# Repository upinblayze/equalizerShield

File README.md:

# Graphic Equalizer Shield

> This project is dependent on [Sparkfun](www.sparkfun.com)'s EAGLE libraries and also OSHPark's DRU file.

## Get EAGLE
The EAGLE download can be found [here](https://www.autodesk.com/products EAGLE/free-download). The free version is sufficient in this case
> EAGLE used to be made by CADSOFT USA, but is now under the AutoDesk umbrella.

## Download and apply design rules
We are going to be using [OSHPark's design rules](https://oshpark.com/LaenPCBOrder.dru) since this is the service we are using to make the PCBs. You should expect a file called LaenPCBOrder.dru

## Clone the repository
For the puposes of simplicity, it is recommended that you clone this repository in your $HOME (root) directory. Input the following command in terminal.

`git clone git@github.com:upinblayze/equalizerShield.git`

## Download Sparkfun's EAGLE libraries
They are made for older versions of EAGLE, but they work nonetheless. You may either clone the [repository](https://github.com/sparkfun/SparkFun EAGLE-Libraries) or download the [zip file]( https://github.com/sparkfun/SparkFun EAGLE-Libraries/archive/master.zip)

## Setup EAGLE Directories

1. Options > Directories...
    * To add a paths by placing colons between each file path to where a the desired directory exists
2. To add the Sparkfun EAGLE libraries in the library field, append `:path/to/SparkFun EAGLE-Libraries-master`. In my case, since I have it in the root directory, I would append `:$HOME/SparkFun EAGLE-Libraries-master`
3. Repeat with the Project field. This is meant for if you do not have a project in the EAGLE created folder. I like to keep my git repositories in the root, so I would append `:$HOME/equalizerShield` to the project field

> You _may_ want to add the DRU (design rules) directory here, however it may be more intuitive to simply use the design rules check to check against OSHPark design specifications

## Open Project

From here you open the project and click on the schematics. You can view the board also by switching view via the `SCH/BRD` button in the tool bar

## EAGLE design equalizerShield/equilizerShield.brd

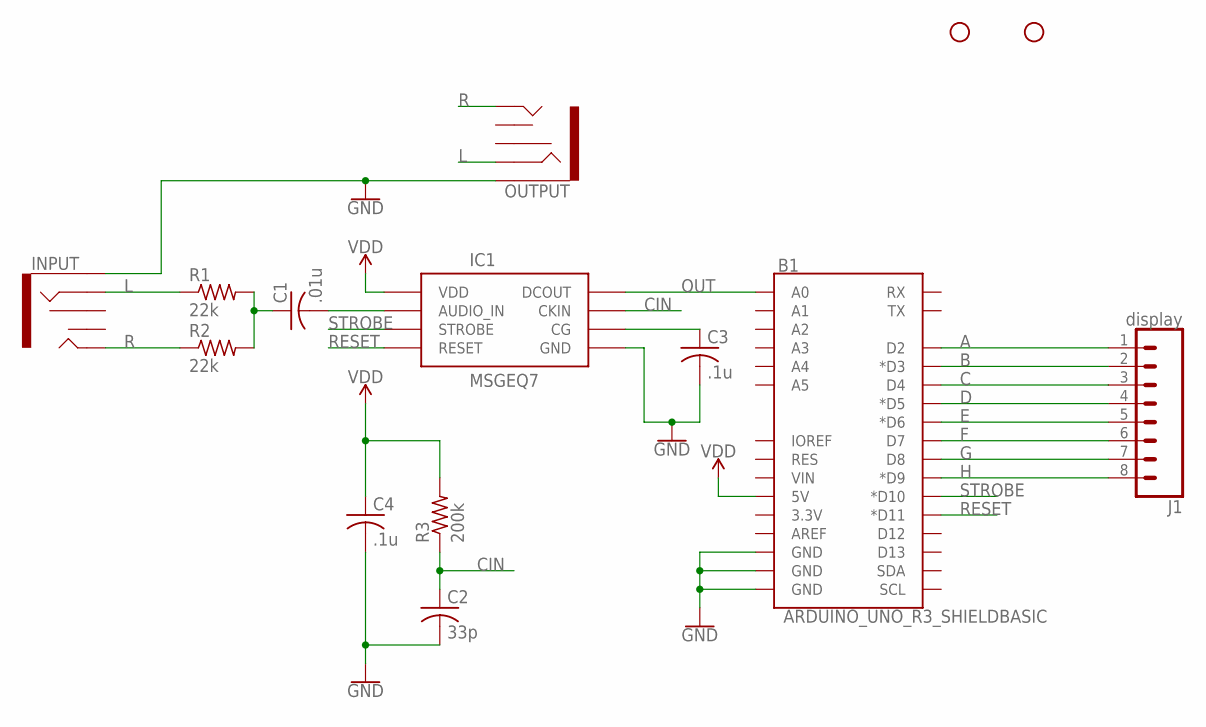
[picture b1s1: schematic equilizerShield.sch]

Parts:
B1: ARDUINO_UNO_R3_SHIELDBASIC; UNO_R3_SHIELD
C1: .01u; C0805
C2: 33p; C0805
C3, C4: .1u; C0805
H1, H2: STAND-OFF
IC1: MSGEQ7P; DIP08
INPUT: AUDIO_JACK_3.5MM_PTH; AUDIO-JACK
J1: display; 1X08_LOCK
OUTPUT: AUDIO_JACK_3.5MM_PTH; AUDIO-JACK
R1, R2: 22k; R0805
R3: 200k; R0805

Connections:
A: B1.D2, J1.1
B: B1.D3 (*D3), J1.2
C: B1.D4, J1.3
CIN: C2.1, IC1.8 (CKIN), R3.1
D: B1.D5 (*D5), J1.4
E: B1.D6 (*D6), J1.5
F: B1.D7, J1.6
G: B1.D8, J1.7
GND: B1.GND@0 (GND), B1.GND@1 (GND), B1.GND@2 (GND), C2.2, C3.2, C4.2, IC1.2 (GND), INPUT.SLEEVE, OUTPUT.SLEEVE
H: B1.D9 (*D9), J1.8
L: INPUT.RING, OUTPUT.RING, R1.1
unnamed: C3.1, IC1.6 (CG)
unnamed: C1.2, IC1.5 (AUDIO_IN)
unnamed: C1.1, R1.2, R2.2
OUT: B1.A0, IC1.3 (DCOUT)
R: INPUT.TIP, OUTPUT.TIP, R2.1
RESET: B1.D11 (*D11), IC1.7 (RESET)
STROBE: B1.D10 (*D10), IC1.4 (STROBE)
VDD: B1.5V, C4.1, IC1.1 (VDD), R3.2

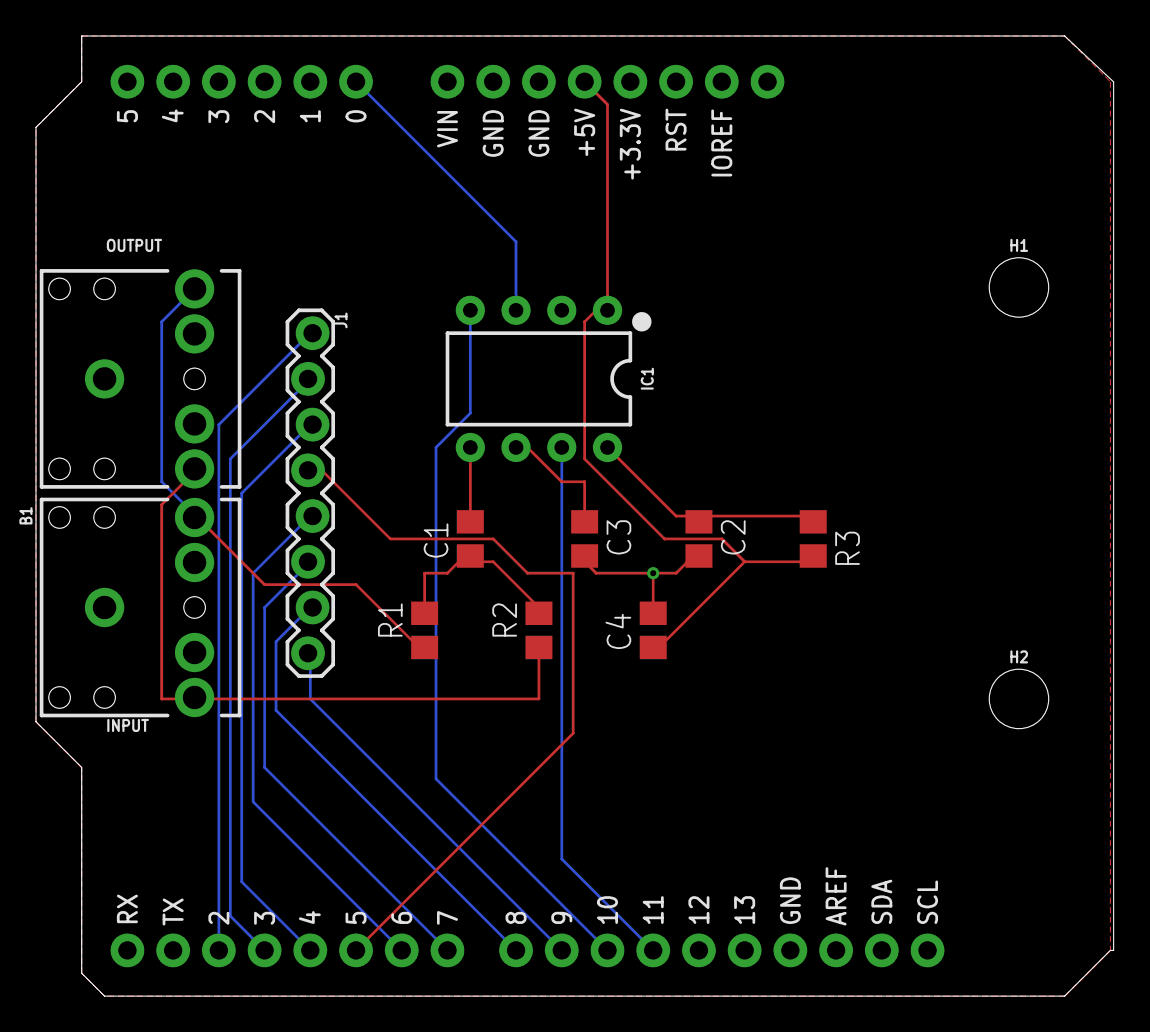
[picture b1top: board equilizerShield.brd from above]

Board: 2 copper layers, 59.9 x 53.3 mm, 14 parts (0 on the bottom side), 19 nets.

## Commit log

2017-06-18 first iteration
2017-06-18 add readme

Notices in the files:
parts and their libraries:
SparkFun-Boards: Licensing: Creative Commons ShareAlike 4.0 International - https://creativecommons.org/licenses/by-sa/4.0
